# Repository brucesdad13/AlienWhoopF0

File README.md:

# AlienWhoopF0

# AlienWhoopF0 Features :alien:
AlienWhoop F0 (code name ZER0) flight controller for Tiny Whoop™, Blade Inductrix™, Eachine™, BetaFPV™, and other micro brushed quadcopter frames. Best in class flight controller running NotFastEnuf Silverware--surface mount soldering required.

* Value-line ST Microelectronics ARM® 32-bit Cortex®-M0 CPU, frequency up to 48 MHz (64MHz with overclocking)
* Invensense MPU-6881 Six-Axis (Gyro + Accelerometer) low power consumption MEMS MotionTracking™ Device
* Latest NotFastEnuf Silverware firmware running the ALIENZER0 target with optional Torque Boost
* Fairchild Semiconductor FDMA410NZ MOSFET with 9.5A continuous and 24A burst brushed motor insanity (8.5mm coreless scream)
* USART1 RX and TX solder pads for external receiver; solder pads for GPIO A13 and A14 for programmable LED strip (SUPER COOL) using WS2812B RGB or low voltage beeper
* Choice of external serial receivers. Officially supporting most SBUS, DSMX, DSM2 and Bayang SPI receivers.

## DIY Flight Controller :alien:
If you fancy doing it yourself (DIY), and have the right equipment and patience, building an AlienWhoop ZER0 from scratch can be tremendously satisfying--though not for the faint of heart. After doing your homework the first step is to place an order for blank PCBs from [OSH Park](https://oshpark.com/shared_projects/yiRaAjtL):
* We recommend ordering the 2oz copper 0.8mm thickness PCB
  * *It takes about three weeks to make the thin boards which allows plenty of time to order components from the bill of materials in the resources folder.*

## Official Facebook page :alien:
AlienWhoop has a Facebook page and it's our preferred way to engage with you and keep you updated. Please Like and/or Follow Us for regular updates in your status feed related to AlienWhoop, DIY electronics, and micro brushed quadcopter related posts.
* http://fb.me/alienwhoop/
* Instagram @alienwhoop

## See the AlienWhoop ZER0 in action on YouTube :alien:

## Acknowledgements :alien:

The AlienWhoop ZER0 Dev Team:

* Brucesdad13 (Charlie)
* Excalibur (Galen)
* MontiFPV (Michael)
* NotFastEnuf (Travis)
* VelcoFPV (Brian)

The sources of inspiration for this board are Lance's AlienFlight F3 Brushed
Quad (CC-BY-SA license) and the Silverware flight controller firmware (MIT
license).

Archival copy of Lance's AlienFlight F3 Eagle CAD Projects
* http://github.com/brucesdad13/AlienFlightArchive

NotFastEnuf's fork of Silverware flight controller firmware:
* https://github.com/NotFastEnuf/NFE_Silverware

~ Please note: **AlienWhoop** is not affiliated with nor endorsed by AlienFlight or forks of Lance's work such as AlienFlight NG. The use of Alien in the name and the alien head vector graphic used on the board silkscreen are nods to the lineage of this remix and to the work of Lance and others who created the conditions for this project to arise. Likewise, AlienWhoop is not affiliated with nor endorsed by Tiny Whoop. The Whoop in the name comes from Jesse Perkin's fantastic Tiny Whoop ("a small first-person-view aircraft that truly allows you to feel the gift of flight and the feeling of being tiny" [tinywhoop.com]) and is simply a nod to his efforts and the TW community worldwide.

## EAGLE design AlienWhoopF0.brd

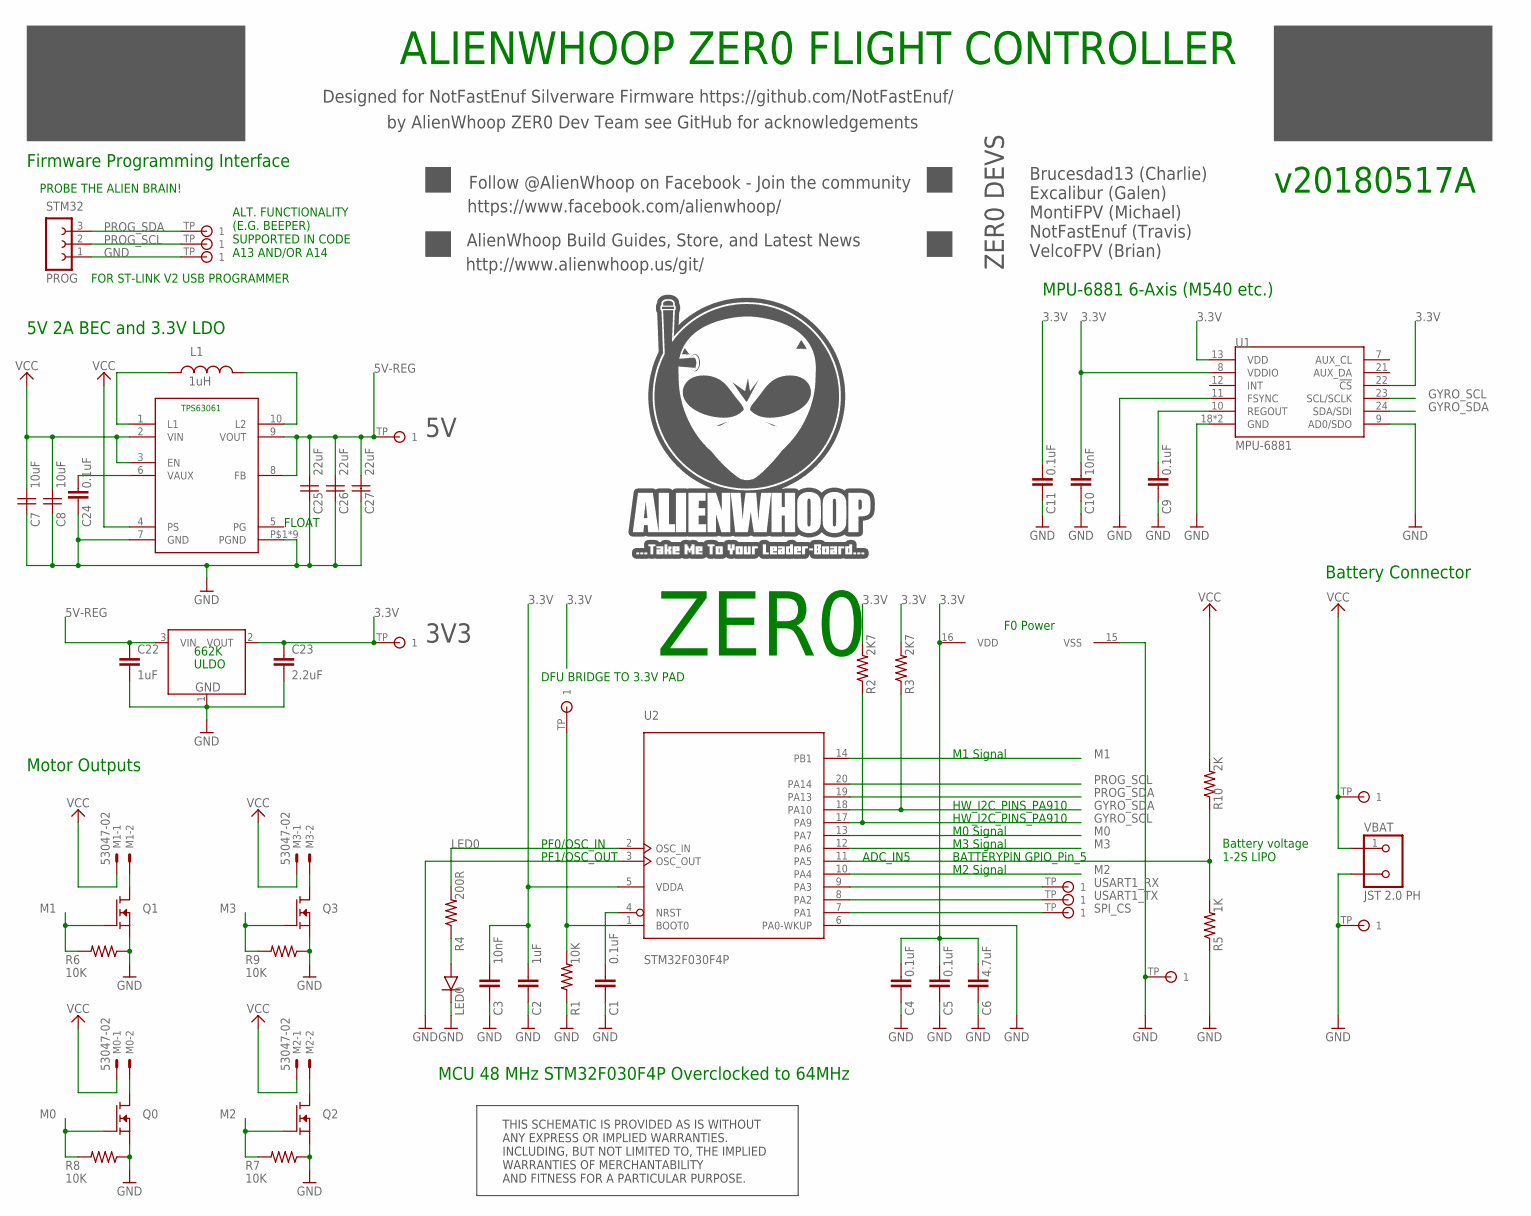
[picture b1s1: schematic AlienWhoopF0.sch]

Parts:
3.3V2, 5V2: TESTPAD
+: TESTPAD
-: TESTPAD
A13, A14: TESTPAD
C1, C4, C5, C9, C11, C24: 0.1uF; 0402; PARTNO GCM155R71C104KA55D
C2, C22: 1uF; 0402; PARTNO GRM155C71A105KE11D
C3, C10: 10nF; 0402; PARTNO GCM155R71H103KA55D
C6: 4.7uF; 0402; PARTNO GRM155R60G475ME47J
C7, C8: 10uF; YUDEN-CAP-0805
C23: 2.2uF; 0402; PARTNO GRM155C70J225KE11D
C25, C26, C27: 22uF; YUDEN-CAP-0805
DFU: TESTPAD
GND23: TESTPAD
GND@2: TESTPAD
L1: 1uH; DFE201612E-INDUCTOR
LED0: BLUE; SMD-CHIP-LED-0805
M0, M1, M2, M3: 53047-02
Q0, Q1, Q2, Q3: FDMA410NZ; MICROFET-2X2
Q5: 3.3V; SOT-23; PARTNO AP2210N-3.3TRG1
R1, R6, R7, R8, R9: 10K; 0402; PARTNO RC0402FR-0710KL
R2, R3: 2K7; 0402; PARTNO AC0402JR-072K7L
R4: 200R; 0402; PARTNO RC0402JR-7D200RL
R5: 1K; 0402; PARTNO AT0402BRD071KL
R10: 2K; 0402; PARTNO AT0402BRE072KL
SPI_CS: TESTPAD
STM32: PROG; FE03-1
U1: MPU-6881; QFN24_PAD; PARTNO MPU-6881
U2: STM32F030F4P; TSSOP20-I; PARTNO STM32F030F4P6TR
U7: TPS63061DSC5V; TPS6306X; PARTNO TPS63061DSCR
U$13, U$14: TESTPAD
VBAT: JST 2.0 PH; S2B-PH-K-S

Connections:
3.3V: 3.3V2.TP, C2.1, C3.1, C4.1, C5.1, C6.1, C10.1, C11.2, C23.1, Q5.2 (VOUT), R2.2, R3.2, U1.8 (VDDIO), U1.13 (VDD), U1.22 (!CS), U2.5 (VDDA), U2.16 (VDD)
5V-REG: 5V2.TP, C22.1, C25.1, C26.1, C27.1, Q5.3 (VIN), U7.8 (FB), U7.9 (VOUT)
BOOT: DFU.TP, R1.2, U2.1 (BOOT0)
GND: -.TP, C1.2, C2.2, C3.2, C4.2, C5.2, C6.2, C7.2, C8.2, C9.2, C10.2, C11.1, C22.2, C23.2, C24.2, C25.2, C26.2, C27.2, GND23.TP, GND@2.TP, LED0.C, Q0.S, Q0.S1 (S), Q1.S, Q1.S1 (S), Q2.S, Q2.S1 (S), Q3.S, Q3.S1 (S), Q5.1 (GND), R1.1, R5.1, R6.1, R7.1, R8.1, R9.1, STM32.1, U1.9 (AD0/SDO), U1.11 (FSYNC), U1.18 (GND), U1.20 (GND), U2.3 (OSC_OUT), U2.6 (PA0-WKUP), U2.15 (VSS), U7.7 (GND), U7.P$1 (PGND), U7.P$2 (PGND), U7.P$3 (PGND), U7.P$4 (PGND), U7.P$5 (PGND), U7.P$17 (PGND), U7.P$18 (PGND), U7.P$21 (PGND), U7.P$22 (PGND), VBAT.2
GYRO_SCL: R2.1, U1.23 (SCL/SCLK), U2.17 (PA9)
GYRO_SDA: R3.1, U1.24 (SDA/SDI), U2.18 (PA10)
L1A: L1.P$1 (1), U7.1 (L1)
L1B: L1.P$2 (2), U7.10 (L2)
LED: LED0.A, R4.1
LED0: R4.2, U2.2 (OSC_IN)
M0: Q0.G, R8.2, U2.13 (PA7)
M0G: M0.2, M0.2S, Q0.D, Q0.D1 (D), Q0.D2 (D), Q0.D3 (D), Q0.D4 (D)
M1: Q1.G, R6.2, U2.14 (PB1)
M1G: M1.2, M1.2S, Q1.D, Q1.D1 (D), Q1.D2 (D), Q1.D3 (D), Q1.D4 (D)
M2: Q2.G, R7.2, U2.10 (PA4)
M2G: M2.2, M2.2S, Q2.D, Q2.D1 (D), Q2.D2 (D), Q2.D3 (D), Q2.D4 (D)
M3: Q3.G, R9.2, U2.12 (PA6)
M3G: M3.2, M3.2S, Q3.D, Q3.D1 (D), Q3.D2 (D), Q3.D3 (D), Q3.D4 (D)
NRST: C1.1, U2.4 (NRST)
PROG_SCL: A14.TP, STM32.2, U2.20 (PA14)
PROG_SDA: A13.TP, STM32.3, U2.19 (PA13)
REGOUT: C9.1, U1.10 (REGOUT)
SPI_CS: SPI_CS.TP, U2.7 (PA1)
USART1_RX: U2.9 (PA3), U$13.TP
USART1_TX: U2.8 (PA2), U$14.TP
VAUX: C24.1, U7.6 (VAUX)
VCC: +.TP, C7.1, C8.1, M0.1, M0.1S, M1.1, M1.1S, M2.1, M2.1S, M3.1, M3.1S, R10.2, U7.2 (VIN), U7.3 (EN), U7.4 (PS), VBAT.1
VOLTDIV: R5.2, R10.1, U2.11 (PA5)

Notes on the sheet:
ADC_IN5
HW_I2C_PINS_PA910
BATTERYPIN GPIO_Pin_5
DFU BRIDGE TO 3.3V PAD
Battery voltage 1-2S LIPO
F0 Power
PF0/OSC_IN
PF1/OSC_OUT
PROBE THE ALIEN BRAIN!
FOR ST-LINK V2 USB PROGRAMMER
Designed for NotFastEnuf Silverware Firmware https://github.com/NotFastEnuf/
https://www.facebook.com/alienwhoop/
Follow @AlienWhoop on Facebook - Join the community
by AlienWhoop ZER0 Dev Team see GitHub for acknowledgements
http://www.alienwhoop.us/git/
AlienWhoop Build Guides, Store, and Latest News
ALIENWHOOP ZER0 FLIGHT CONTROLLER
v20180517A
THIS SCHEMATIC IS PROVIDED AS IS WITHOUT ANY EXPRESS OR IMPLIED WARRANTIES. INCLUDING, BUT NOT LIMITED TO, THE IMPLIED WARRANTIES OF MERCHANTABILITY AND FITNESS FOR A PARTICULAR PURPOSE.
Motor Outputs
MPU-6881 6-Axis (M540 etc.)
Battery Connector
5V 2A BEC and 3.3V LDO
Firmware Programming Interface
ZER0
MCU 48 MHz STM32F030F4P Overclocked to 64MHz
Brucesdad13 (Charlie) Excalibur (Galen) MontiFPV (Michael) NotFastEnuf (Travis) VelcoFPV (Brian)
ZER0 DEVS
3V3
ALT. FUNCTIONALITY (E.G. BEEPER) SUPPORTED IN CODE A13 AND/OR A14
M2 Signal
M0 Signal
M1 Signal
M3 Signal
FLOAT
662K

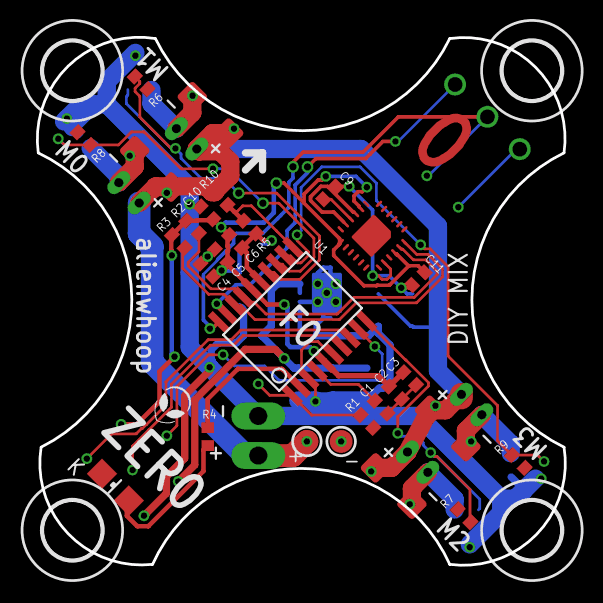
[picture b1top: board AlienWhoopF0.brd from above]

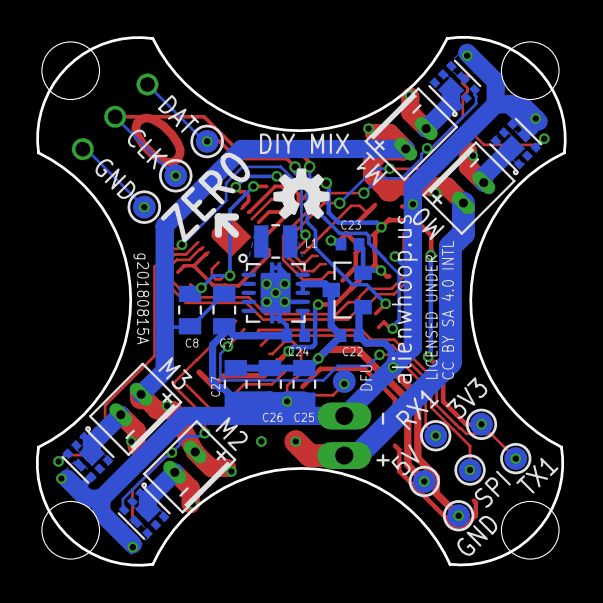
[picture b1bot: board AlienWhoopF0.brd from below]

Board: 2 copper layers, 29.3 x 29.3 mm, 60 parts (31 on the bottom side), 28 nets.

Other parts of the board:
LOGO3: OSHW-LOGOS; OSHW-LOGO-S
U$1, U$2, U$3, U$4: 3,2

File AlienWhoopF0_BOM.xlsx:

Qty | Value | Part Num | Package | Parts | Comments
6 | 0.1uF | GCM155R71C104KA55D | 0402 | C1, C4, C5, C9, C11, C24 | Can substitute
5 | 10K | RC0402FR-0710KL | 0402 | R1, R6, R7, R8, R9 | Can substitute
4 | 53047-02 | 53047-0210 | 53047-02 | M0, M1, M2, M3 | Molex motor plugs; can substitute 2-pin 1.25mm pitch shrouded
4 | FDMA410NZ | FDMA410NZ | MICROFET-2X2 | Q0, Q1, Q2, Q3 | For better performance use Infineon IRFHS8342TRP
3 | 22UF | JMK212BJ226MG-T | YUDEN-CAP-0805 | C25, C26, C27 | Can substitute
2 | 2K7 | AC0402JR-072K7L | 0402 | R2, R3 | For I2C gyro; can substitute/change value to find optimal performance
2 | 10nF | GCM155R71H103KA55D | 0402 | C3, C10 | Can substitute
2 | 1uF | GRM155C71A105KE11D | 0402 | C2, C22 | Can substitute
2 | 10UF | JMK212AB7106KG-T | YUDEN-CAP-0805 | C7, C8 | Can substitute
1 | 3.3V | AP2210N-3.3TRG1 | SOT-23 | Q5 | Don't use AP2210N! Use LM6206N3 (662K); can be harvested from toy fc/tx
1 | BLUE | APHCM2012QBC/D-F01 | SMD-CHIP-LED-0805 | LED0 | Blue LED; can substitute--update CLR as necessary
1 | 1K | AT0402BRD071KL | 0402 | R5 | For voltage divider; can substitute
1 | 2K | AT0402BRE072KL | 0402 | R10 | For voltage divider; can substitute
1 | 1UH | DFE201612E-1R0M=P2 | DFE201612E-INDUCTOR | L1 | Can substitute
1 | 2.2uF | GRM155C70J225KE11D | 0402 | C23 | Can substitute
1 | 4.7uF | GRM155R60G475ME47J | 0402 | C6 | Can substitute
1 | MPU-6881 | MPU-6881 | QFN24_PAD | U1 | Can substitute Invensense MPU-6500, MPU-9250, etc; update NFE gyro code
1 | 200R | RC0402JR-7D200RL | 0402 | R4 | Current limiting resistor (CLR) for LED0; match to LED0 datasheet
1 | STM32F030F4P | STM32F030F4P6TR | TSSOP20-I | U2 | MCU
1 | TPS63061DSC5V | TPS63061DSCR | TPS6306X | U7 | Buck boost

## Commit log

2018-08-15 Initial commit of the AlienWhoop ZER0 DIY MIX. #sendit #alienwhoopzer0
2019-05-19 Sharpened up corners to better grip grommets during crashes--consistent with manuf. fc. Added BOM as requested; closes PR#2
2019-05-19 Update README.md
    Updated board preview image and OSH Park PCB shared project link

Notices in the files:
AlienWhoopF0.brd:
LICENSED UNDER
CC BY SA 4.0 INTL
parts and their libraries:
SparkFun-Aesthetics: Licensing: Creative Commons ShareAlike 4.0 International - https://creativecommons.org/licenses/by-sa/4.0
alienflight: License: CC BY SA
alienflight: Released under the Creative Commons
Attribution Share-Alike 4.0 License
http://creativecommons.org/licenses/by-sa/4.0
